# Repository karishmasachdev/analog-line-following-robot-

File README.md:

# analog-line-following-robot — Custom PCB Design

A line-following robot built entirely from discrete analog components — no microcontroller, no programmable logic. This repo covers the full circuit design and my custom KiCad schematic/PCB layout, built on top of a line-following robot.

## Overview

The robot follows a black line on a white surface using visible-light sensing, analog comparison, and transistor-driven motors — all without any digital logic or code. The signal path has three stages:

- **Sensing** — a pair of LDR (photoresistor) voltage dividers, each paired with a white LED that actively floods the surface below the robot with light
- **Comparison** — the LM358 package's two op-amps are each wired as a comparator using the same left-row and right-row voltages, but with the `+`/`−` inputs swapped between them: one op-amp takes the left row on `+` and the right row on `−`, the other takes the right row on `+` and the left row on `−`. This produces two separate, naturally complementary outputs — one op-amp per motor — instead of a single shared output
- **Actuation** — the comparator output drives BJTs (acting as switches) that control current to two DC gear motors, steering the robot by adjusting each wheel's power independently

## How it works

Each LDR sits in a voltage divider with its own potentiometer, one row for the left sensor and one for the right. When a surface reflects more light back into an LDR, that LDR's resistance drops and its row's voltage falls; over the black line, less light returns, resistance rises, and the row's voltage climbs. The two rows are compared directly against each other rather than against a fixed threshold.

Each op-amp takes the left row's voltage and the right row's voltage as its two inputs, but with the `+` and `−` connections reversed relative to the other op-amp. Because of that reversal, when one side reads higher than the other, the two op-amp outputs snap in opposite directions — one goes high while the other goes low — rather than passing through a slow analog gradient. Each output feeds the base of its own NPN BJT, switching that motor's current on or off. Flyback diodes across each motor protect the transistors from voltage spikes when the motor switches off, and electrolytic capacitors across the power rails smooth out ripple from the motors starting and stopping.

Because the two op-amp outputs are naturally complementary (one high while the other is low, and vice versa), the two motors respond oppositely to the same left-vs-right comparison: when the robot drifts and one sensor row reads higher relative to the other, one motor speeds up while the other slows or stops, steering the robot back onto the line.

## Repo contents

```
├── kicad/              KiCad project, schematic, and PCB layout files
├── images/
│   ├── schematic.png
│   ├── pcb-layout.png
│   └── 3d-render.png
└── media/
    └── demo-video link
```

## Schematic

## PCB layout (routed)

## 3D render

## Demo

https://github.com/user-attachments/assets/1498a725-2bcb-41b3-9672-68c0f6f58ff7

## Key components

| Part | Role |
|---|---|
| LM358 dual op-amp | Voltage comparator, two channels wired with reversed inputs |
| CdS photoresistor (LDR) x2 | Reflected-light sensing |
| White LED x2 | Active illumination of the surface |
| PN2222 NPN BJT x2 | Motor switching stage |
| N20 gear motor x2 | Differential drive |
| 10k potentiometer x2 | Sensor calibration / balancing |
| 1N4001 diode x2 | Motor flyback protection |
| 100µF electrolytic capacitor x2 | Power rail smoothing |

## Tools used

- KiCad (schematic capture, PCB layout, ERC/DRC)
- LTspice (circuit simulation, sensor and comparator characterization)
- Oscilloscope (hardware verification of LED/motor drive signals)
- Soldering iron (hand-soldered sensor and wiring connections)

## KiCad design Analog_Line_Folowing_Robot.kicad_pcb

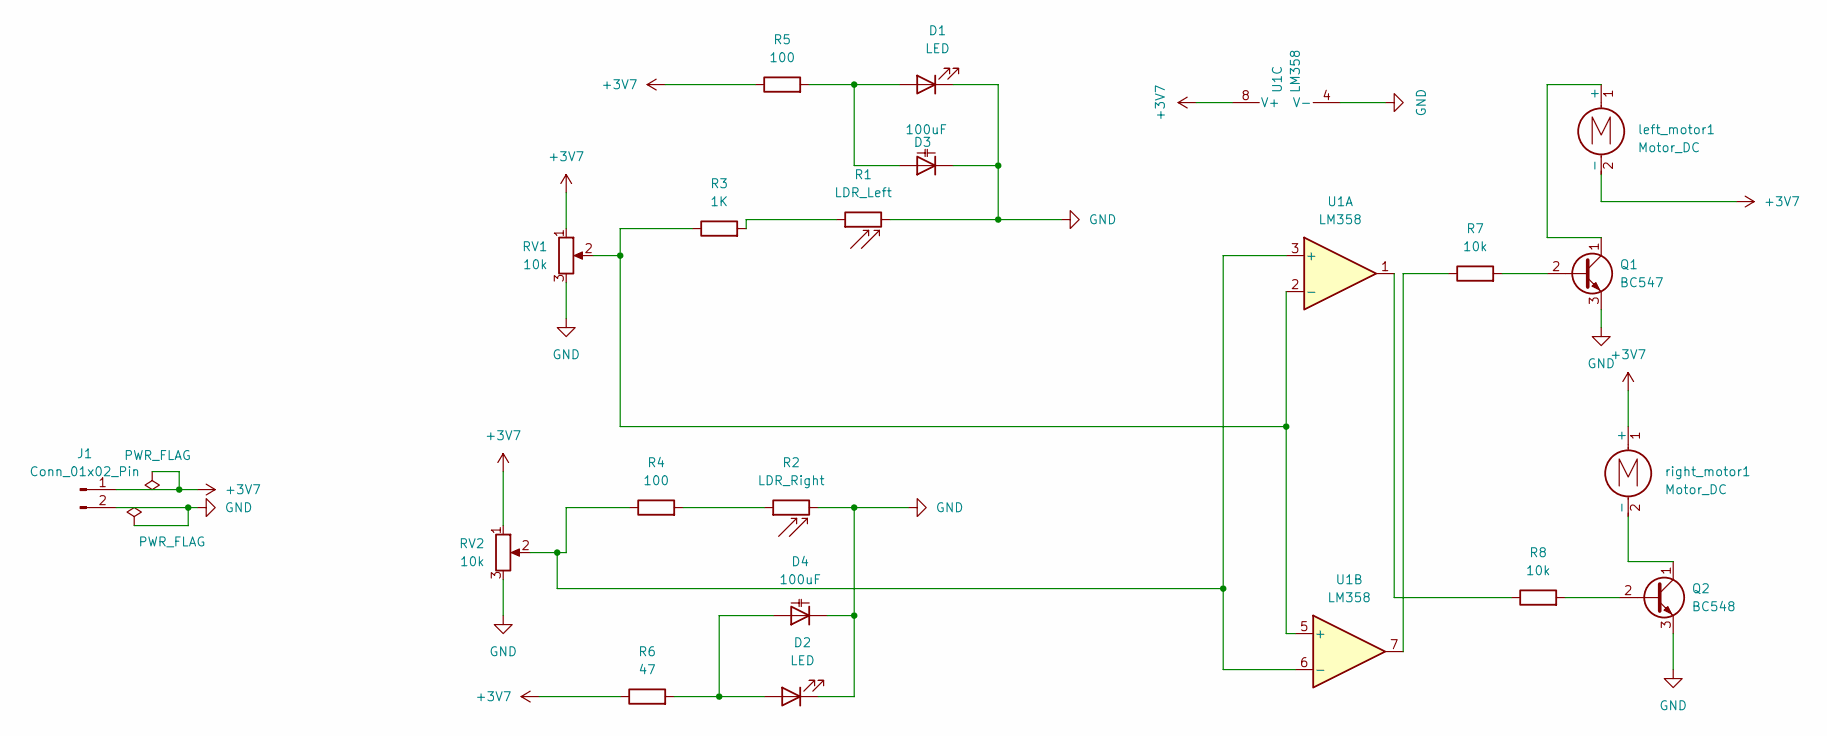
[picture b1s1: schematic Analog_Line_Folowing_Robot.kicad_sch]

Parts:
D1, D2: LED; LED_D5.0mm
D3, D4: 100uF; CP_Radial_D5.0mm_P2.00mm
J1: Conn_01x02_Pin; PinHeader_1x02_P2.54mm_Vertical
Q1: BC547; TO-92_Inline
Q2: BC548; TO-92_Inline
R1: LDR_Left; R_LDR_4.9x4.2mm_P2.54mm_Vertical
R2: LDR_Right; R_LDR_4.9x4.2mm_P2.54mm_Vertical
R3: 1K; R_Axial_DIN0207_L6.3mm_D2.5mm_P2.54mm_Vertical
R4, R5: 100; R_Axial_DIN0207_L6.3mm_D2.5mm_P2.54mm_Vertical
R6: 47; R_Axial_DIN0207_L6.3mm_D2.5mm_P2.54mm_Vertical
R7, R8: 10k; R_Axial_DIN0207_L6.3mm_D2.5mm_P2.54mm_Vertical
RV1, RV2: 10k; Potentiometer_Bourns_3386X_Horizontal
U1: LM358; DIP-8-16_W7.62mm
left_motor1: Motor_DC; PinHeader_1x02_P2.54mm_Vertical
right_motor1: Motor_DC; PinHeader_1x02_P2.54mm_Vertical

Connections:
+3V7: J1.1, R5.1, R6.1, RV1.1, RV2.1, U1.8 (V+), left_motor1.2 (-), right_motor1.1 (+)
GND: D1.1 (K), D2.1 (K), D3.1 (K), D4.1 (K), J1.2, Q1.3 (E), Q2.3 (E), R1.2, R2.2, RV1.3, RV2.3, U1.4 (V-)
unnamed: D1.2 (A), D3.2 (A), R5.2
unnamed: D2.2 (A), D4.2 (A), R6.2
unnamed: Q1.2 (B), R7.2
unnamed: Q1.1 (C), left_motor1.1 (+)
unnamed: Q2.2 (B), R8.2
unnamed: Q2.1 (C), right_motor1.2 (-)
unnamed: R1.1, R3.2
unnamed: R2.1, R4.2
unnamed: R7.1, U1.7
unnamed: R8.1, U1.1
unnamed: R4.1, RV2.2, U1.3 (+), U1.6 (-)
unnamed: R3.1, RV1.2, U1.2 (-), U1.5 (+)

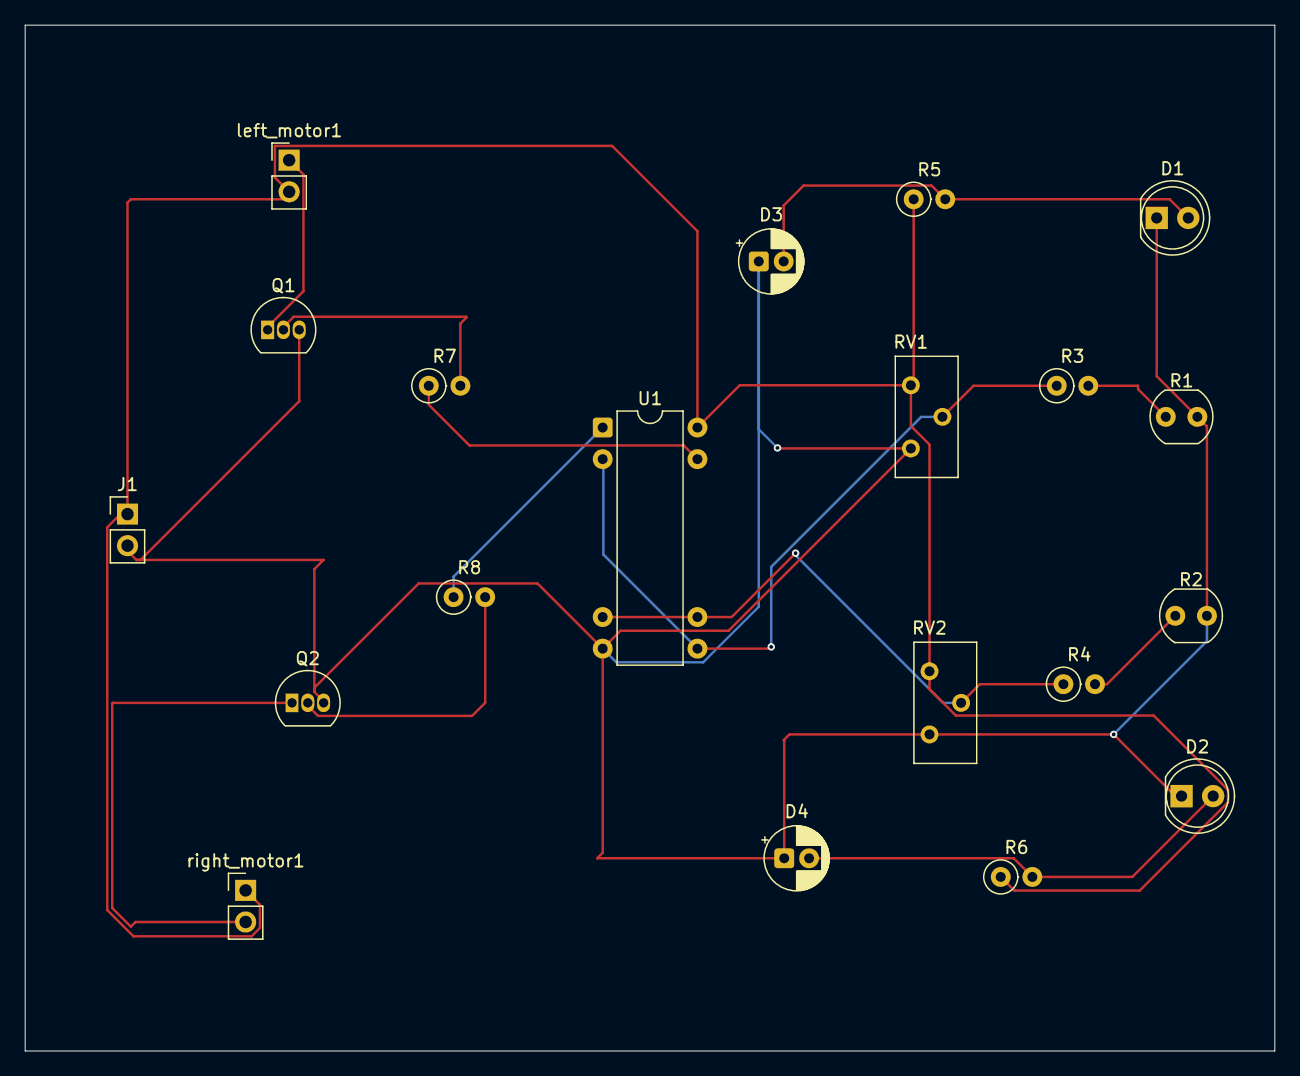
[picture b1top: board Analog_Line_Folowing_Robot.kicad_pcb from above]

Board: 2 copper layers, 100.5 x 82.5 mm, 20 parts (0 on the bottom side), 14 nets.
